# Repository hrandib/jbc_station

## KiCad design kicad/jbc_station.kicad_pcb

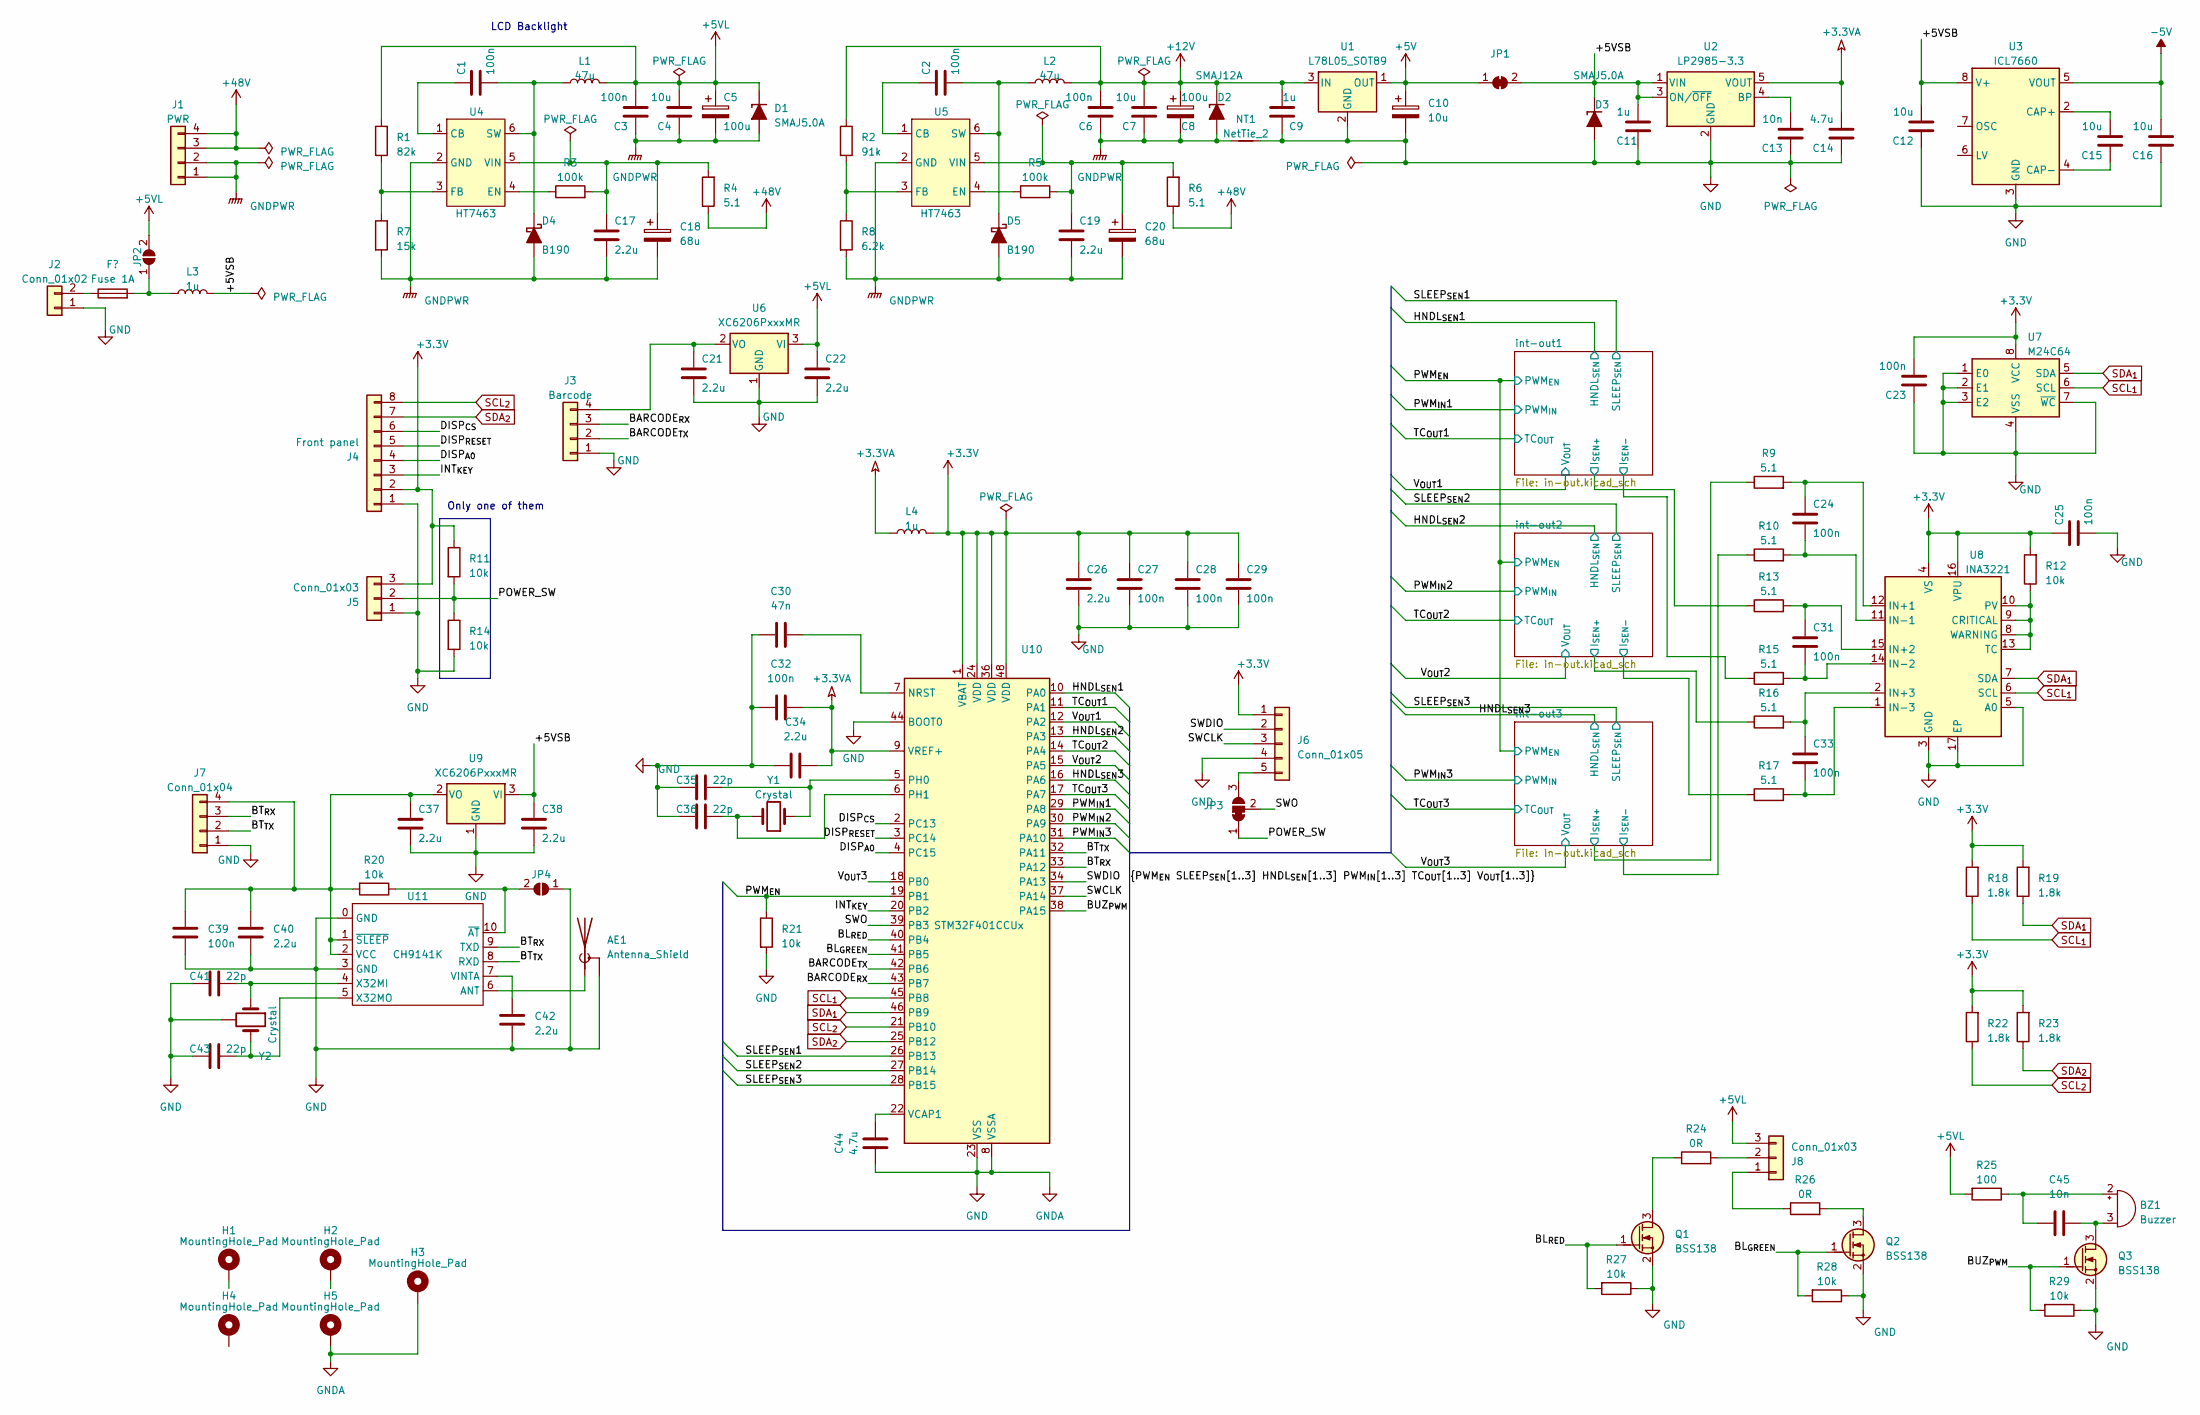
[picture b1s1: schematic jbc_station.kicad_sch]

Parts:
AE1: Antenna_Shield; Texas_SWRA117D_2.4GHz_Left
BZ1: Buzzer; BUZ_5020
C1, C2, C3, C6, C23, C24, C25, C31, C33: 100n; C_0805_2012Metric
C4, C7, C12, C15, C16: 10u; C_0805_2012Metric
C5, C8: 100u; C_Radial_D8.0mm_H11.5mm_P3.50mm
C9, C11: 1u; C_0805_2012Metric
C10: 10u; C_1812_4532Metric
C13, C45: 10n; C_0805_2012Metric
C14: 4.7u; C_0805_2012Metric
C17, C19, C21, C22, C26, C34, C37, C38: 2.2u; C_0805_2012Metric
C18, C20: 68u; C_Radial_D8.0mm_H11.5mm_P3.50mm
C27, C28, C29, C32, C39: 100n; C_0603_1608Metric_Pad1.08x0.95mm_HandSolder
C30: 47n; C_0805_2012Metric
C35, C36, C41, C43: 22p; C_0805_2012Metric
C40, C42: 2.2u; C_1206_3216Metric_Pad1.33x1.80mm_HandSolder
C44: 4.7u; C_1206_3216Metric_Pad1.33x1.80mm_HandSolder
D1, D3: SMAJ5.0A; D_SMA
D2: SMAJ12A; D_SMA
D4, D5: B190; D_SMA
F1: Fuse 1A; Fuseholder_Littelfuse_Nano2_154x
H1, H2, H3, H4, H5: MountingHole_Pad; MountingHole_3.2mm_M3_DIN965_Pad_TopBottom
J1: PWR; PhoenixContact_MCV_1,5_4-G-3.5_1x04_P3.50mm_Vertical
J2: Conn_01x02; JST_EH_B2B-EH-A_1x02_P2.50mm_Vertical
J3: Barcode; JST_EH_B4B-EH-A_1x04_P2.50mm_Vertical
J4: Front panel; JST_EH_B8B-EH-A_1x08_P2.50mm_Vertical
J5, J8: Conn_01x03; JST_EH_B3B-EH-A_1x03_P2.50mm_Vertical
J6: Conn_01x05; PinHeader_1x05_P2.54mm_Vertical
J7: Conn_01x04; PinHeader_1x04_P2.54mm_Vertical
JP1: SolderJumper_2_Bridged; SolderJumper-2_P1.3mm_Bridged_RoundedPad1.0x1.5mm
JP2, JP4: SolderJumper_2_Open; SolderJumper-2_P1.3mm_Open_TrianglePad1.0x1.5mm
JP3: SolderJumper_3_Bridged12; SolderJumper-3_P1.3mm_Bridged12_RoundedPad1.0x1.5mm_NumberL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
L1, L2: 47u; L_7.3x7.3_H3.5
L3, L4: 1u; L_1206_3216Metric_Pad1.22x1.90mm_HandSolder
NT1: NetTie_2; NetTie-2_SMD_Pad2.0mm
Q1, Q2, Q3: BSS138; SOT-23
R1: 82k; R_0603_1608Metric_Pad0.98x0.95mm_HandSolder
R2: 91k; R_0603_1608Metric_Pad0.98x0.95mm_HandSolder
R3, R5: 100k; R_0603_1608Metric_Pad0.98x0.95mm_HandSolder
R4, R6: 5.1; R_1206_3216Metric_Pad1.30x1.75mm_HandSolder
R7: 15k; R_0603_1608Metric_Pad0.98x0.95mm_HandSolder
R8: 6.2k; R_0603_1608Metric_Pad0.98x0.95mm_HandSolder
R9, R10, R13, R15, R16, R17: 5.1; R_0805_2012Metric_Pad1.20x1.40mm_HandSolder
R11, R14, R20, R21, R27, R28, R29: 10k; R_0805_2012Metric_Pad1.20x1.40mm_HandSolder
R12: 10k; R_0603_1608Metric_Pad0.98x0.95mm_HandSolder
R18, R19, R22, R23: 1.8k; R_0603_1608Metric_Pad0.98x0.95mm_HandSolder
R24, R26: 0R; R_1206_3216Metric_Pad1.30x1.75mm_HandSolder
R25: 100; R_0805_2012Metric_Pad1.20x1.40mm_HandSolder
U1: L78L05_SOT89; SOT-89-3
U2: LP2985-3.3; SOT-23-5
U3: ICL7660; SOIC-8_3.9x4.9mm_P1.27mm
U4, U5: HT7463; SOT-23-6_Handsoldering
U6, U9: XC6206PxxxMR; SOT-23-3
U7: M24C64; SOIC-8_3.9x4.9mm_P1.27mm
U8: INA3221; Texas_RGV_S-PVQFN-N16_EP2.1x2.1mm
U10: STM32F401CCUx; QFN-48-1EP_7x7mm_P0.5mm_EP5.6x5.6mm
U11: CH9141K; ESSOP-10_3.9x4.9mm_P1.00mm
Y1: Crystal; Crystal_SMD_5032-2Pin_5.0x3.2mm
Y2: Crystal; Crystal_SMD_3225-4Pin_3.2x2.5mm_HandSoldering

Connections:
+3.3V: C23.2, C25.1, C26.1, C27.1, C28.1, C29.1, J4.2, J5.3, J6.1, L4.2, R11.1, R12.2, R18.2, R19.2, R22.2, R23.2, U7.8 (VCC), U8.4 (VS), U8.16 (VPU), U10.1 (VBAT), U10.24 (VDD), U10.36 (VDD), U10.48 (VDD); also elsewhere on the board
+3.3VA: C14.2, C32.2, C34.2, L4.1, U2.5 (VOUT), U10.9 (VREF+)
+5V: C10.1, JP1.1 (A), U1.1 (OUT); also elsewhere on the board
+5VL: C3.2, C4.2, C5.1, C22.1, D1.1 (K), J8.3, JP2.2 (B), L1.2, R1.1, R25.2, U6.3 (VI)
+12V: C6.2, C7.2, C8.1, C9.2, D2.1 (K), L2.2, R2.1, U1.3 (IN); also elsewhere on the board
+48V: J1.3, J1.4, R4.1, R6.1; also elsewhere on the board
-5V: C16.2, U3.5 (VOUT); also elsewhere on the board
/+5VSB: C11.2, C12.2, C38.1, D3.1 (K), JP1.2 (B), L3.2, U2.1 (VIN), U2.3 (ON/~OFF), U3.8 (V+), U9.3 (VI)
/BARCODE_{RX}: J3.3, U10.43 (PB7)
/BARCODE_{TX}: J3.2, U10.42 (PB6)
/BL_{GREEN}: Q2.1 (G), R28.2, U10.41 (PB5)
/BL_{RED}: Q1.1 (G), R27.2, U10.40 (PB4)
/BT_{RX}: J7.3, U10.33 (PA12), U11.9 (TXD)
/BT_{TX}: J7.2, U10.32 (PA11), U11.8 (RXD)
/BUZ_{PWM}: Q3.1 (G), R29.2, U10.38 (PA15)
/DISP_{A0}: J4.4, U10.4 (PC15)
/DISP_{CS}: J4.6, U10.2 (PC13)
/DISP_{RESET}: J4.5, U10.3 (PC14)
/HNDL_{SEN}1: U10.10 (PA0); also elsewhere on the board
/HNDL_{SEN}2: U10.13 (PA3); also elsewhere on the board
/HNDL_{SEN}3: U10.16 (PA6); also elsewhere on the board
/INT_{KEY}: J4.3, U10.20 (PB2)
/POWER_SW: J5.2, JP3.1 (A), R11.2, R14.1
/PWM_{EN}: R21.1, U10.19 (PB1); also elsewhere on the board
/PWM_{IN}1: U10.29 (PA8); also elsewhere on the board
/PWM_{IN}2: U10.30 (PA9); also elsewhere on the board
/PWM_{IN}3: U10.31 (PA10); also elsewhere on the board
/SLEEP_{SEN}1: U10.26 (PB13); also elsewhere on the board
/SLEEP_{SEN}2: U10.27 (PB14); also elsewhere on the board
/SLEEP_{SEN}3: U10.28 (PB15); also elsewhere on the board
/SWCLK: J6.3, U10.37 (PA14)
/SWDIO: J6.2, U10.34 (PA13)
/SWO: JP3.2 (C), U10.39 (PB3)
/TC_{OUT}1: U10.11 (PA1); also elsewhere on the board
/TC_{OUT}2: U10.14 (PA4); also elsewhere on the board
/TC_{OUT}3: U10.17 (PA7); also elsewhere on the board
/V_{OUT}1: U10.12 (PA2); also elsewhere on the board
/V_{OUT}2: U10.15 (PA5); also elsewhere on the board
/V_{OUT}3: U10.18 (PB0); also elsewhere on the board
/int-out1/I_{SEN+}: R13.1; also elsewhere on the board
/int-out1/I_{SEN-}: R15.1; also elsewhere on the board
/int-out2/I_{SEN+}: R16.1; also elsewhere on the board
/int-out2/I_{SEN-}: R17.1; also elsewhere on the board
/int-out3/I_{SEN+}: R9.1; also elsewhere on the board
/int-out3/I_{SEN-}: R10.1; also elsewhere on the board
GND: AE1.2 (Shield), C9.1, C10.2, C11.1, C12.1, C13.1, C14.1, C16.1, C21.2, C22.2, C23.1, C25.2, C26.2, C27.2, C28.2, C29.2, C30.1, C32.1, C34.1, C35.2, C36.2, C37.2, C38.2, C39.1, C40.1, C41.2, C42.1, C43.2, C44.1, D3.2 (A), H3.1, H5.1, J2.1, J3.1, J4.1, J5.1, J6.4, J7.1, JP4.1 (A), NT1.2, Q1.2 (S), Q2.2 (S), Q3.2 (S), R14.2, R21.2, R27.1, R28.1, R29.1, U1.2 (GND), U2.2 (GND), U3.3 (GND), U6.1 (GND), U7.1 (E0), U7.2 (E1), U7.3 (E2), U7.4 (VSS), U7.7 (~WC), U8.3 (GND), U8.5 (A0), U8.17 (EP), U9.1 (GND), U10.8 (VSSA), U10.23 (VSS), U10.35 (VSS), U10.44 (BOOT0), U10.47 (VSS), U10.49 (VSS), U11.0 (GND), U11.3 (GND), Y2.2, Y2.4; also elsewhere on the board
GNDPWR: C3.1, C4.1, C5.2, C6.1, C7.1, C8.2, C17.2, C18.2, C19.2, C20.2, D1.2 (A), D2.2 (A), D4.2 (A), D5.2 (A), J1.1, J1.2, NT1.1, R7.2, R8.2, U4.2 (GND), U5.2 (GND); also elsewhere on the board
unnamed: AE1.1 (A), U11.6 (ANT)
unnamed: BZ1.2 (+), C45.1, R25.1
unnamed: BZ1.3 (-), C45.2, Q3.3 (D)
unnamed: C1.2, D4.1 (K), L1.1, U4.6 (SW)
unnamed: C2.2, D5.1 (K), L2.1, U5.6 (SW)
unnamed: F1.1, J2.2
unnamed: C21.1, J3.4, U6.2 (VO)
unnamed: J6.5, JP3.3 (B)
unnamed: C37.1, C39.2, C40.2, J7.4, R20.2, U9.2 (VO), U11.1 (~SLEEP), U11.2 (VCC)
unnamed: J8.1, R26.1
unnamed: J8.2, R24.2
unnamed: F1.2, JP2.1 (A), L3.1
unnamed: JP4.2 (B), R20.1, U11.10 (~AT)
unnamed: Q1.3 (D), R24.1
unnamed: Q2.3 (D), R26.2
unnamed: C13.2, U2.4 (BP)
unnamed: C15.2, U3.2 (CAP+)
unnamed: C15.1, U3.4 (CAP-)
unnamed: C1.1, U4.1 (CB)
unnamed: R3.1, U4.4 (EN)
unnamed: R1.2, R7.1, U4.3 (FB)
unnamed: C17.1, C18.1, R3.2, R4.2, U4.5 (VIN)
unnamed: C2.1, U5.1 (CB)
unnamed: R5.1, U5.4 (EN)
unnamed: R2.2, R8.1, U5.3 (FB)
unnamed: C19.1, C20.1, R5.2, R6.2, U5.5 (VIN)
unnamed: R12.1, U8.8 (WARNING), U8.9 (CRITICAL), U8.10 (PV), U8.13 (TC)
unnamed: C24.1, R9.2, U8.12 (IN+1)
unnamed: C31.1, R13.2, U8.15 (IN+2)
unnamed: C33.1, R16.2, U8.2 (IN+3)
unnamed: C24.2, R10.2, U8.11 (IN-1)
unnamed: C31.2, R15.2, U8.14 (IN-2)
unnamed: C33.2, R17.2, U8.1 (IN-3)
unnamed: C30.2, U10.7 (NRST)
unnamed: C35.1, U10.5 (PH0), Y1.1
unnamed: C36.1, U10.6 (PH1), Y1.2
unnamed: C44.2, U10.22 (VCAP1)
unnamed: C42.2, U11.7 (VINTA)
unnamed: C41.1, U11.4 (X32MI), Y2.1
unnamed: C43.1, U11.5 (X32MO), Y2.3
SCL_{1}: R18.1, U7.6 (SCL), U8.6 (SCL), U10.45 (PB8)
SCL_{2}: J4.8, R22.1, U10.21 (PB10)
SDA_{1}: R19.1, U7.5 (SDA), U8.7 (SDA), U10.46 (PB9)
SDA_{2}: J4.7, R23.1, U10.25 (PB12)

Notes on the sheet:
LCD Backlight
Only one of them

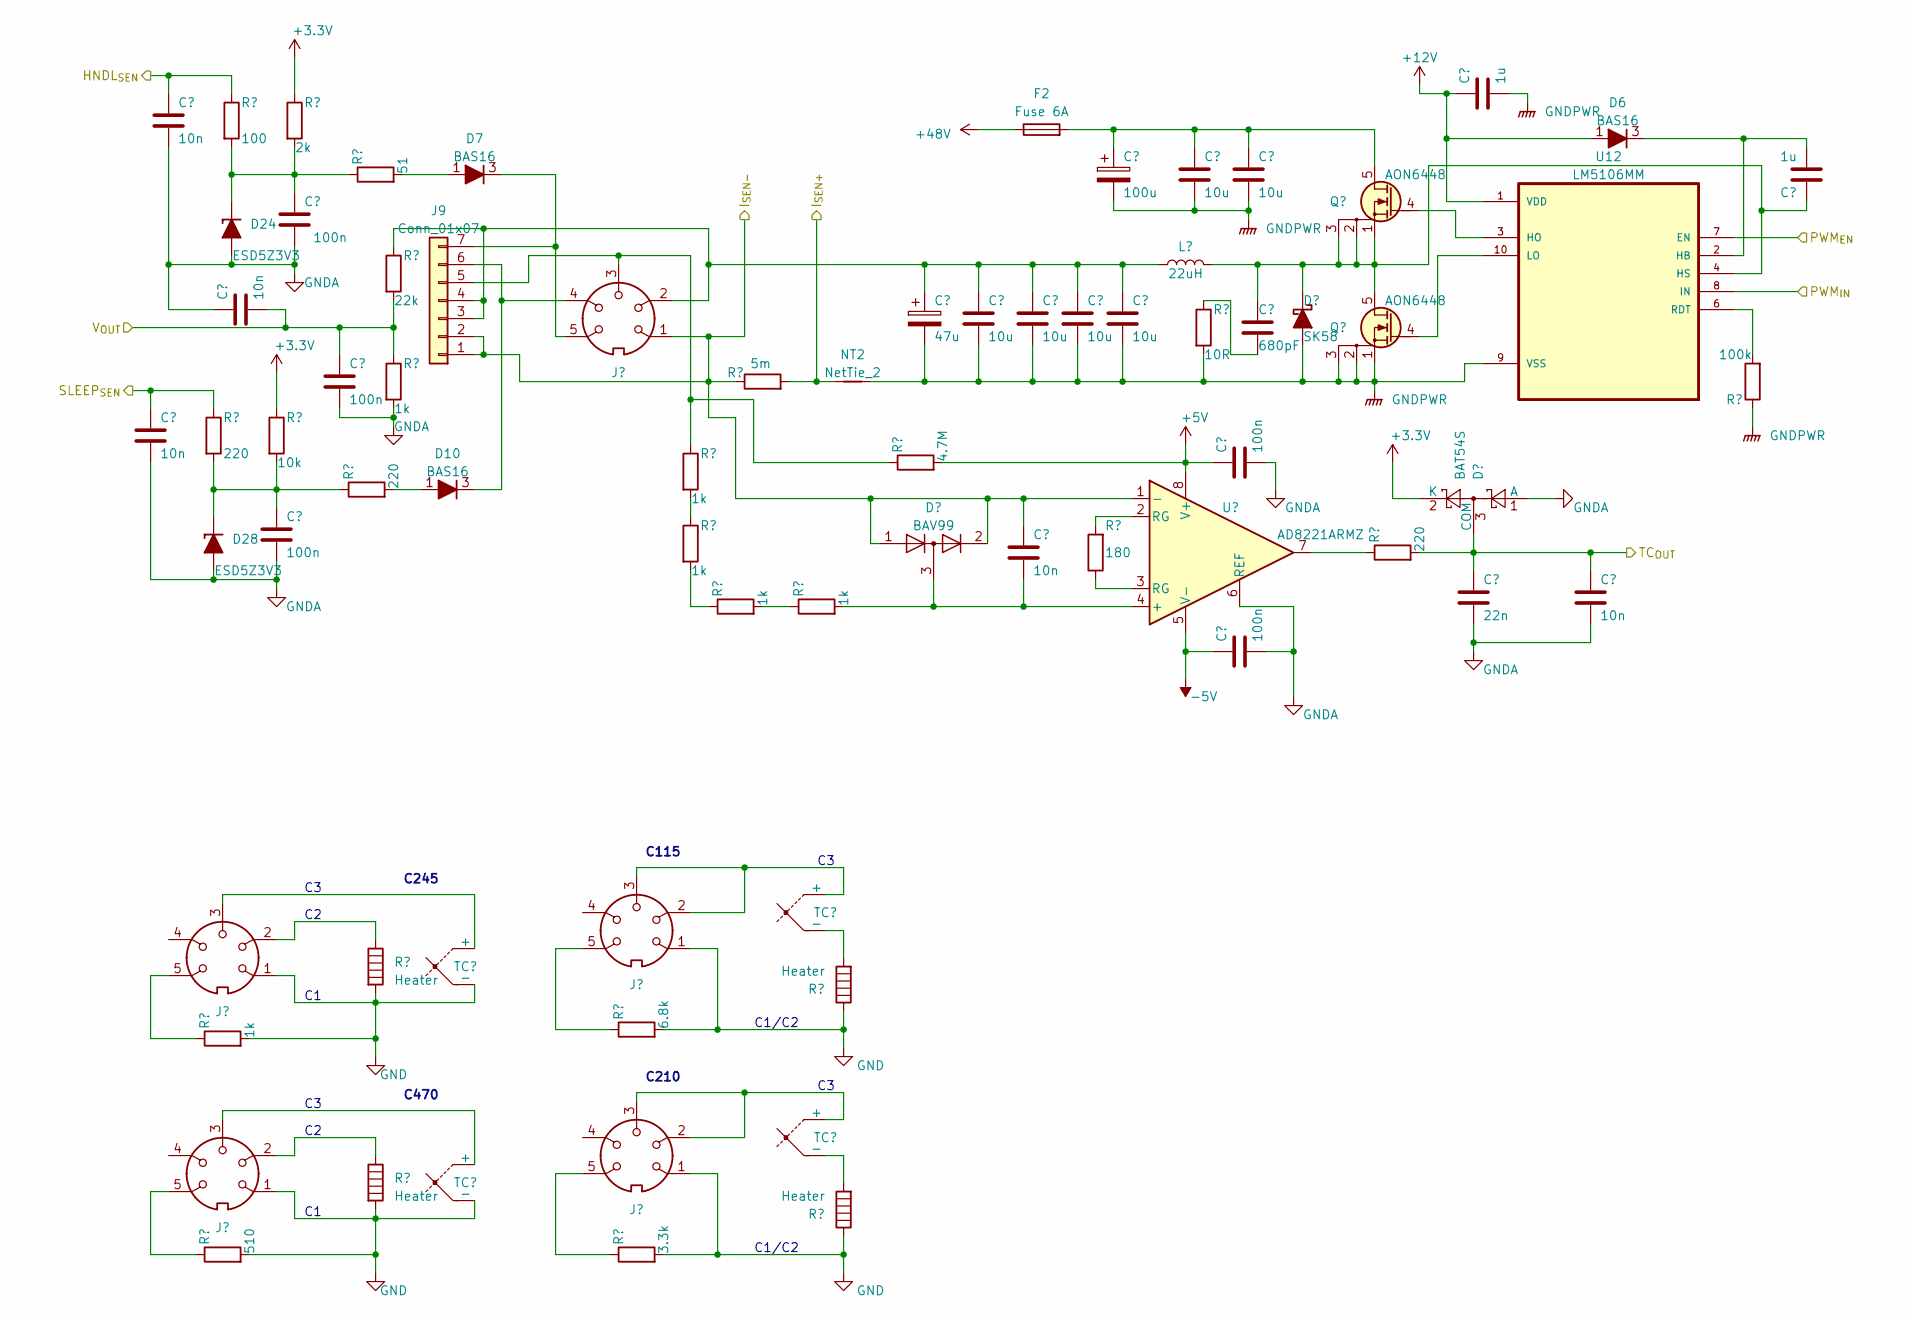
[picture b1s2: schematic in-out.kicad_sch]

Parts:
C46, C51: 1u; C_1206_3216Metric
C47, C53, C61, C66: 10n; C_0402_1005Metric
C48: 100u; C_Radial_D8.0mm_H11.5mm_P3.50mm
C49, C50, C55, C56, C57, C58: 10u; C_2220_5650Metric
C52, C60, C62, C63, C67: 100n; C_0603_1608Metric_Pad1.08x0.95mm_HandSolder
C54: 47u; C_Radial_D8.0mm_H11.5mm_P3.50mm
C59: 680pF; C_0805_2012Metric
C64: 10n; C_0805_2012Metric
C65: 22n; C_0805_2012Metric
D6, D7, D10: BAS16; SOT-23
D9: SK58; D_SMB-SMC_Universal
D11: BAT54S; SOT-23
D13: BAV99; SOT-23
D24: ESD5Z3V3; D_SOD-523_TVS
D28: ESD5Z3V3; D_SOD-523
F2: Fuse 6A; Fuseholder_Littelfuse_Nano2_154x
J9: Conn_01x07; JST_EH_B7B-EH-A_1x07_P2.50mm_Vertical
J10, J11, J12, J13, J14: DIN-5
L5: 22uH; L_Bourns_SRP1770TA_16.9x16.9mm
NT2: NetTie_2; NetTie-2_SMD_Pad2.0mm
Q4, Q5: AON6448; Infineon_PG-TDSON-8
R30: 100; R_0603_1608Metric_Pad0.98x0.95mm_HandSolder
R31: 2k; R_0603_1608Metric_Pad0.98x0.95mm_HandSolder
R32: 51; R_0603_1608Metric_Pad0.98x0.95mm_HandSolder
R33: 22k; R_0603_1608Metric_Pad0.98x0.95mm_HandSolder
R34: 10R; R_1206_3216Metric_Pad1.30x1.75mm_HandSolder
R35: 1k; R_0603_1608Metric_Pad0.98x0.95mm_HandSolder
R36: 5m; R_2512_6332Metric_Pad1.40x3.35mm_HandSolder
R37: 100k; R_0603_1608Metric_Pad0.98x0.95mm_HandSolder
R38, R42, R45: 220; R_0603_1608Metric_Pad0.98x0.95mm_HandSolder
R39: 10k; R_0603_1608Metric_Pad0.98x0.95mm_HandSolder
R40: 4.7M; R_1206_3216Metric_Pad1.30x1.75mm_HandSolder
R41, R43, R46, R47: 1k; R_1206_3216Metric_Pad1.30x1.75mm_HandSolder
R44: 180; R_0603_1608Metric_Pad0.98x0.95mm_HandSolder
R48, R49, R52, R53: Heater
R50: 6.8k
R51: 1k
R54: 510
R55: 3.3k; R_0603_1608Metric_Pad0.98x0.95mm_HandSolder
TC1, TC2, TC3, TC4: Thermocouple
U12: LM5106MM; MSOP-10_3x3mm_P0.5mm
U13: AD8221ARMZ; MSOP-8_3x3mm_P0.65mm

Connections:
+3.3V: D11.2 (K), R31.1, R39.1; also elsewhere on the board
+5V: C62.1, R40.2, U13.8 (V+); also elsewhere on the board
+12V: C46.1, D6.1 (A), U12.1 (VDD); also elsewhere on the board
+48V: F2.1; also elsewhere on the board
-5V: C67.1, U13.5 (V-); also elsewhere on the board
/HNDL_{SEN}1: C47.1, R30.1; also elsewhere on the board
/PWM_{EN}: U12.7 (EN); also elsewhere on the board
/PWM_{IN}1: U12.8 (IN); also elsewhere on the board
/SLEEP_{SEN}1: C61.1, R38.1; also elsewhere on the board
/TC_{OUT}1: C65.1, C66.1, D11.3 (COM), R45.2; also elsewhere on the board
/V_{OUT}1: C53.2, C60.1, R33.2, R35.1; also elsewhere on the board
/int-out1/I_{SEN+}: NT2.1, R36.2; also elsewhere on the board
/int-out1/I_{SEN-}: C64.1, D13.1 (K), D13.2 (A), J9.1, J9.2, R36.1, U13.1 (-); also elsewhere on the board
GND: C47.2, C52.2, C53.1, C60.2, C61.2, C62.2, C63.2, C65.2, C66.2, C67.2, D11.1 (A), D24.2 (A), D28.2 (A), R35.2, U13.6 (REF); also elsewhere on the board
GNDPWR: C46.2, C48.2, C49.2, C50.2, C54.2, C55.2, C56.2, C57.2, C58.2, D9.2 (A), NT2.2, Q5.1 (S), Q5.2 (S), Q5.3 (S), R34.2, R37.1, U12.9 (VSS); also elsewhere on the board
unnamed: C59.2, R34.1
unnamed: C51.2, D6.3 (K), U12.2 (HB)
unnamed: D7.1 (A), R32.2
unnamed: D7.3 (K), J9.7
unnamed: C51.1, C59.1, D9.1 (K), L5.2, Q4.1 (S), Q4.2 (S), Q4.3 (S), Q5.5 (D), U12.4 (HS)
unnamed: D10.1 (A), R42.2
unnamed: D10.3 (K), J9.6
unnamed: C54.1, C55.1, C56.1, C57.1, C58.1, J9.3, J9.4, L5.1, R33.1
unnamed: J9.5, R40.1, R41.1
unnamed: J11.1, J12.1, J13.1, J14.1, R48.2, R49.1, R50.2, R51.2, R52.2, R53.1, R54.2, R55.2, TC2.2 (-), TC4.2 (-)
unnamed: J11.2, J11.3, TC1.1 (+)
unnamed: J11.5, R50.1
unnamed: J12.2, R48.1
unnamed: J12.3, TC2.1 (+)
unnamed: J12.5, R51.1
unnamed: J13.2, J13.3, TC3.1 (+)
unnamed: J13.5, R55.1
unnamed: J14.2, R52.1
unnamed: J14.3, TC4.1 (+)
unnamed: J14.5, R54.1
unnamed: C48.1, C49.1, C50.1, F2.2, Q4.5 (D)
unnamed: Q4.4 (G), U12.3 (HO)
unnamed: Q5.4 (G), U12.10 (LO)
unnamed: R41.2, R43.1
unnamed: R43.2, R46.1
unnamed: R44.1, U13.3 (RG)
unnamed: R44.2, U13.2 (RG)
unnamed: R45.1, U13.7
unnamed: R46.2, R47.1
unnamed: R49.2, TC1.2 (-)
unnamed: R53.2, TC3.2 (-)
unnamed: R37.2, U12.6 (RDT)
unnamed: C64.2, D13.3 (K), R47.2, U13.4 (+)

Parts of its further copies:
C68, C73, C90, C95: 1u; C_1206_3216Metric
C69, C75, C83, C88, C91, C97, C105, C110: 10n; C_0402_1005Metric
C70, C92: 100u; C_Radial_D8.0mm_H11.5mm_P3.50mm
C71, C72, C77, C78, C79, C80, C93, C94, C99, C100, C101, C102: 10u; C_2220_5650Metric
C74, C82, C84, C85, C89, C96, C104, C106, C107, C111: 100n; C_0603_1608Metric_Pad1.08x0.95mm_HandSolder
C76, C98: 47u; C_Radial_D8.0mm_H11.5mm_P3.50mm
C81, C103: 680pF; C_0805_2012Metric
C86, C108: 10n; C_0805_2012Metric
C87, C109: 22n; C_0805_2012Metric
D8, D16: ESD5Z3V3; D_SOD-523_TVS
D12, D20: ESD5Z3V3; D_SOD-523
D14, D15, D18, D22, D23, D26: BAS16; SOT-23
D17, D25: SK58; D_SMB-SMC_Universal
D19, D27: BAT54S; SOT-23
D21, D29: BAV99; SOT-23
F3, F4: Fuse 6A; Fuseholder_Littelfuse_Nano2_154x
J15, J21: Conn_01x07; JST_EH_B7B-EH-A_1x07_P2.50mm_Vertical
L6, L7: 22uH; L_Bourns_SRP1770TA_16.9x16.9mm
NT3, NT4: NetTie_2; NetTie-2_SMD_Pad2.0mm
Q6, Q7, Q8, Q9: AON6448; Infineon_PG-TDSON-8
R56, R82: 100; R_0603_1608Metric_Pad0.98x0.95mm_HandSolder
R57, R83: 2k; R_0603_1608Metric_Pad0.98x0.95mm_HandSolder
R58, R84: 51; R_0603_1608Metric_Pad0.98x0.95mm_HandSolder
R59, R85: 22k; R_0603_1608Metric_Pad0.98x0.95mm_HandSolder
R60, R86: 10R; R_1206_3216Metric_Pad1.30x1.75mm_HandSolder
R61, R87: 1k; R_0603_1608Metric_Pad0.98x0.95mm_HandSolder
R62, R88: 5m; R_2512_6332Metric_Pad1.40x3.35mm_HandSolder
R63, R89: 100k; R_0603_1608Metric_Pad0.98x0.95mm_HandSolder
R64, R68, R71, R90, R94, R97: 220; R_0603_1608Metric_Pad0.98x0.95mm_HandSolder
R65, R91: 10k; R_0603_1608Metric_Pad0.98x0.95mm_HandSolder
R66, R92: 4.7M; R_1206_3216Metric_Pad1.30x1.75mm_HandSolder
R67, R69, R72, R73, R93, R95, R98, R99: 1k; R_1206_3216Metric_Pad1.30x1.75mm_HandSolder
R70, R96: 180; R_0603_1608Metric_Pad0.98x0.95mm_HandSolder
U14, U16: LM5106MM; MSOP-10_3x3mm_P0.5mm
U15, U17: AD8221ARMZ; MSOP-8_3x3mm_P0.65mm

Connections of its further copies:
+3.3V: D19.2 (K), D27.2 (K), R57.1, R65.1, R83.1, R91.1; also elsewhere on the board
+5V: C84.1, C106.1, R66.2, R92.2, U15.8 (V+), U17.8 (V+); also elsewhere on the board
+12V: C68.1, C90.1, D14.1 (A), D22.1 (A), U14.1 (VDD), U16.1 (VDD); also elsewhere on the board
+48V: F3.1, F4.1; also elsewhere on the board
-5V: C89.1, C111.1, U15.5 (V-), U17.5 (V-); also elsewhere on the board
/HNDL_{SEN}2: C69.1, R56.1; also elsewhere on the board
/HNDL_{SEN}3: C91.1, R82.1; also elsewhere on the board
/PWM_{EN}: U14.7 (EN), U16.7 (EN); also elsewhere on the board
/PWM_{IN}2: U14.8 (IN); also elsewhere on the board
/PWM_{IN}3: U16.8 (IN); also elsewhere on the board
/SLEEP_{SEN}2: C83.1, R64.1; also elsewhere on the board
/SLEEP_{SEN}3: C105.1, R90.1; also elsewhere on the board
/TC_{OUT}2: C87.1, C88.1, D19.3 (COM), R71.2; also elsewhere on the board
/TC_{OUT}3: C109.1, C110.1, D27.3 (COM), R97.2; also elsewhere on the board
/V_{OUT}2: C75.2, C82.1, R59.2, R61.1; also elsewhere on the board
/V_{OUT}3: C97.2, C104.1, R85.2, R87.1; also elsewhere on the board
/int-out2/I_{SEN+}: NT3.1, R62.2; also elsewhere on the board
/int-out2/I_{SEN-}: C86.1, D21.1 (K), D21.2 (A), J15.1, J15.2, R62.1, U15.1 (-); also elsewhere on the board
/int-out3/I_{SEN+}: NT4.1, R88.2; also elsewhere on the board
/int-out3/I_{SEN-}: C108.1, D29.1 (K), D29.2 (A), J21.1, J21.2, R88.1, U17.1 (-); also elsewhere on the board
GND: C69.2, C74.2, C75.1, C82.2, C83.2, C84.2, C85.2, C87.2, C88.2, C89.2, C91.2, C96.2, C97.1, C104.2, C105.2, C106.2, C107.2, C109.2, C110.2, C111.2, D8.2 (A), D12.2 (A), D16.2 (A), D19.1 (A), D20.2 (A), D27.1 (A), R61.2, R87.2, U15.6 (REF), U17.6 (REF); also elsewhere on the board
GNDPWR: C68.2, C70.2, C71.2, C72.2, C76.2, C77.2, C78.2, C79.2, C80.2, C90.2, C92.2, C93.2, C94.2, C98.2, C99.2, C100.2, C101.2, C102.2, D17.2 (A), D25.2 (A), NT3.2, NT4.2, Q7.1 (S), Q7.2 (S), Q7.3 (S), Q9.1 (S), Q9.2 (S), Q9.3 (S), R60.2, R63.1, R86.2, R89.1, U14.9 (VSS), U16.9 (VSS); also elsewhere on the board
unnamed: C81.2, R60.1
unnamed: C103.2, R86.1
unnamed: C73.2, D14.3 (K), U14.2 (HB)
unnamed: D15.1 (A), R58.2
unnamed: D15.3 (K), J15.7
unnamed: C74.1, D16.1 (K), R56.2, R57.2, R58.1
unnamed: C73.1, C81.1, D17.1 (K), L6.2, Q6.1 (S), Q6.2 (S), Q6.3 (S), Q7.5 (D), U14.4 (HS)
unnamed: D18.1 (A), R68.2
unnamed: D18.3 (K), J15.6
unnamed: C85.1, D20.1 (K), R64.2, R65.2, R68.1
unnamed: C95.2, D22.3 (K), U16.2 (HB)
unnamed: D23.1 (A), R84.2
unnamed: D23.3 (K), J21.7
unnamed: C95.1, C103.1, D25.1 (K), L7.2, Q8.1 (S), Q8.2 (S), Q8.3 (S), Q9.5 (D), U16.4 (HS)
unnamed: D26.1 (A), R94.2
unnamed: D26.3 (K), J21.6
unnamed: C76.1, C77.1, C78.1, C79.1, C80.1, J15.3, J15.4, L6.1, R59.1
unnamed: J15.5, R66.1, R67.1
unnamed: C98.1, C99.1, C100.1, C101.1, C102.1, J21.3, J21.4, L7.1, R85.1
unnamed: J21.5, R92.1, R93.1
unnamed: C70.1, C71.1, C72.1, F3.2, Q6.5 (D)
unnamed: Q6.4 (G), U14.3 (HO)
unnamed: Q7.4 (G), U14.10 (LO)
unnamed: C92.1, C93.1, C94.1, F4.2, Q8.5 (D)
unnamed: Q8.4 (G), U16.3 (HO)
unnamed: Q9.4 (G), U16.10 (LO)
unnamed: R67.2, R69.1
unnamed: R69.2, R72.1
unnamed: R70.1, U15.3 (RG)
unnamed: R70.2, U15.2 (RG)
unnamed: R71.1, U15.7
unnamed: R72.2, R73.1
unnamed: R93.2, R95.1
unnamed: R95.2, R98.1
unnamed: R96.1, U17.3 (RG)
unnamed: R96.2, U17.2 (RG)
unnamed: R97.1, U17.7
unnamed: R98.2, R99.1
unnamed: R63.2, U14.6 (RDT)
unnamed: C86.2, D21.3 (K), R73.2, U15.4 (+)
unnamed: R89.2, U16.6 (RDT)
unnamed: C108.2, D29.3 (K), R99.2, U17.4 (+)

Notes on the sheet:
C245
C1/C2
C210
C470
C115

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
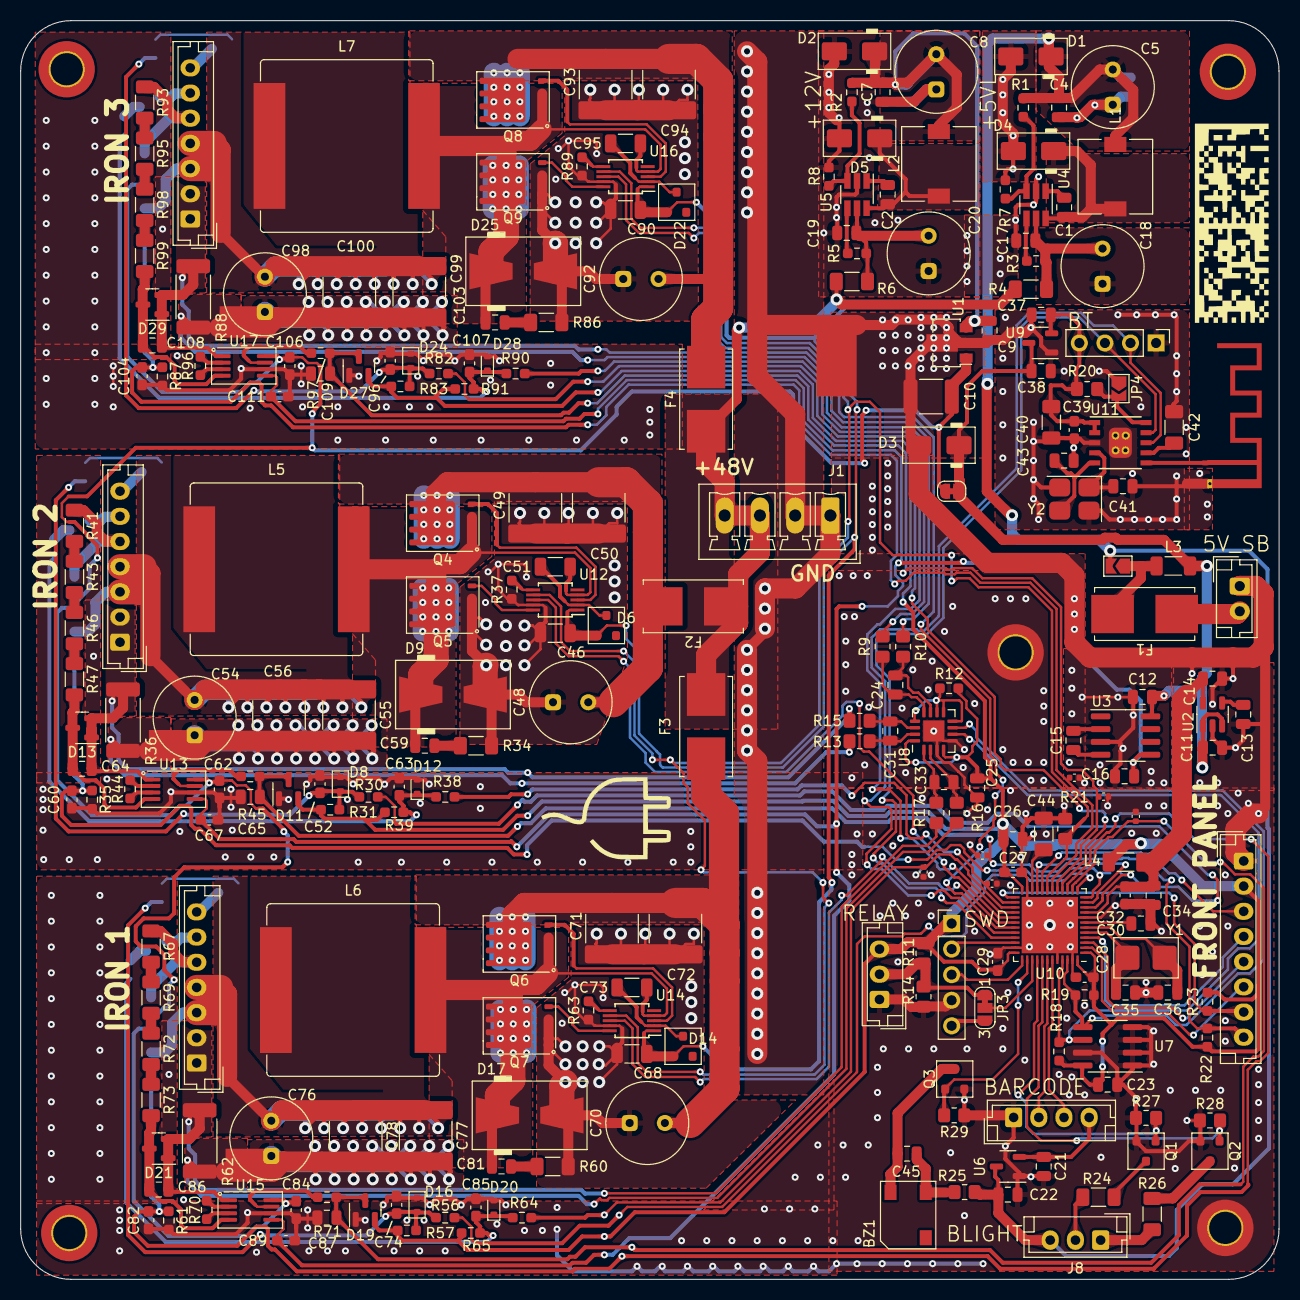
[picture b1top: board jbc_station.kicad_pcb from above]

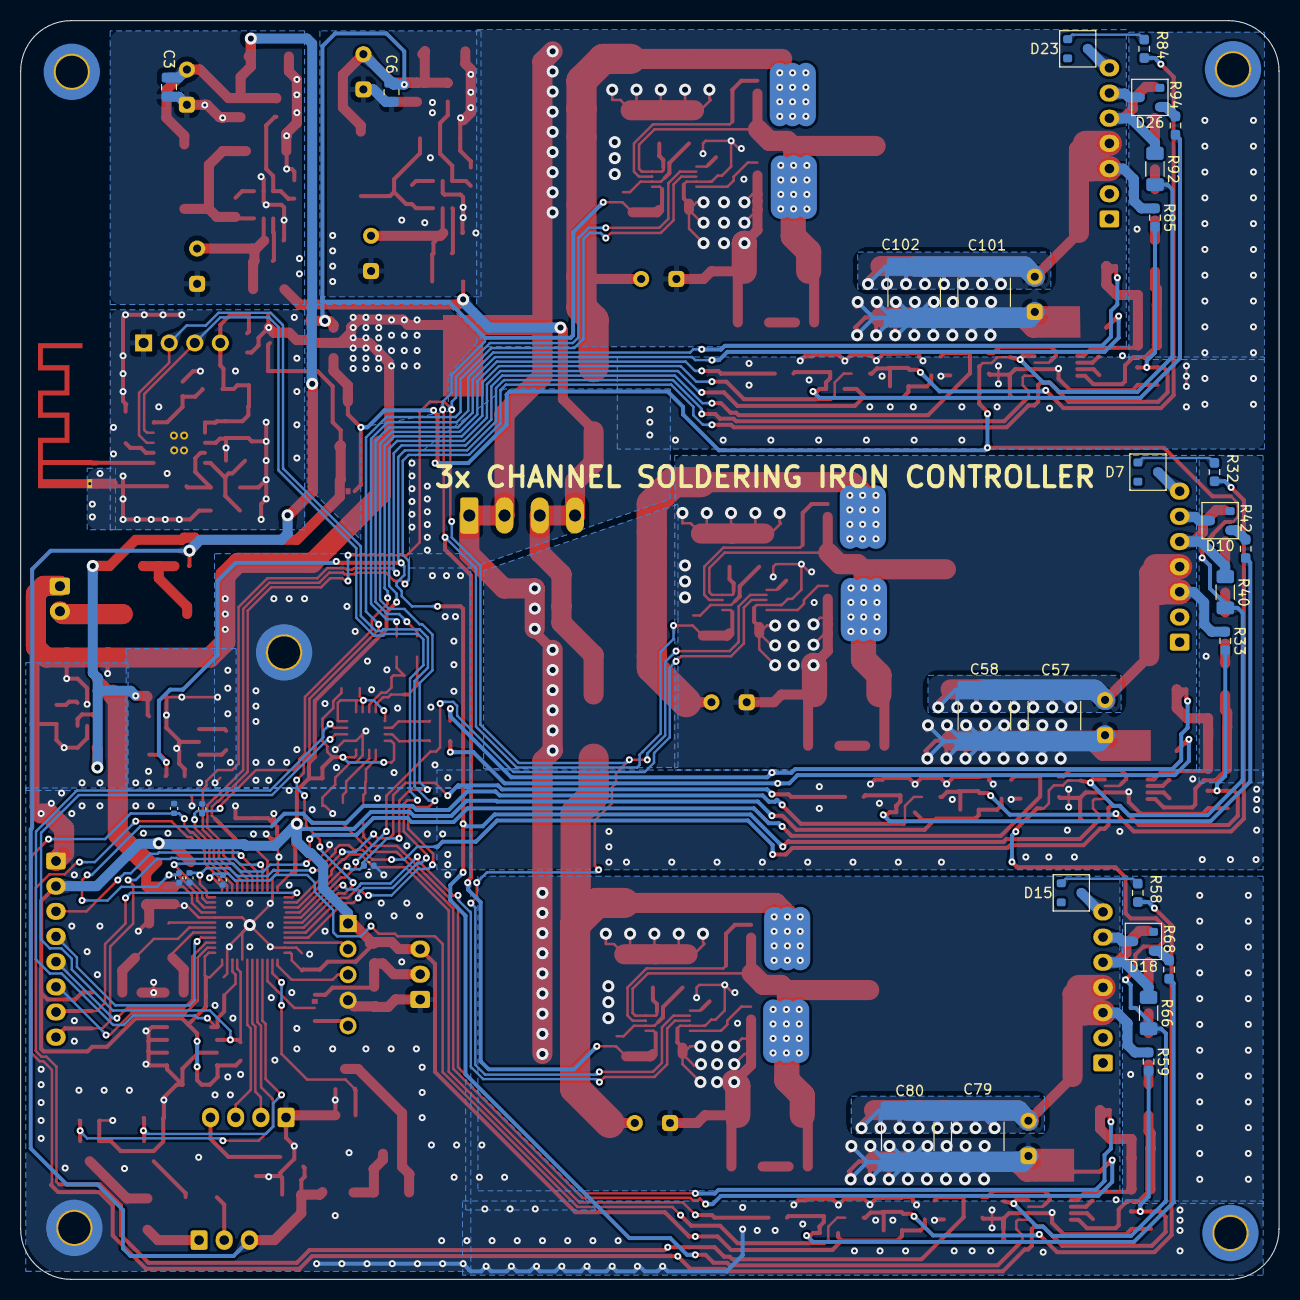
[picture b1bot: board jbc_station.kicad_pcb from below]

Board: 2 copper layers, 125.0 x 125.0 mm, 288 parts (32 on the bottom side), 157 nets.

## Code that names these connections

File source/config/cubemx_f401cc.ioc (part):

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Mcu.Name=STM32F401C(B-C)Ux
Mcu.Package=UFQFPN48
Mcu.UserName=STM32F401CCUx
PA0-WKUP.GPIOParameters=GPIO_Label,GPIO_Mode
PA0-WKUP.GPIO_Label=HNDL_SEN1
PA0-WKUP.GPIO_Mode=GPIO_MODE_ANALOG
PA0-WKUP.Signal=ADCx_IN0
PA1.GPIOParameters=GPIO_Label,GPIO_Mode
PA1.GPIO_Label=TC1
PA1.GPIO_Mode=GPIO_MODE_ANALOG
PA1.Signal=ADCx_IN1
PA10.GPIOParameters=GPIO_Speed,GPIO_Label
PA10.GPIO_Label=PWM3
PA10.GPIO_Speed=GPIO_SPEED_FREQ_MEDIUM
PA10.Signal=S_TIM1_CH3
PA11.GPIOParameters=GPIO_Speed,GPIO_Label
PA11.GPIO_Label=BT_TX
PA11.GPIO_Speed=GPIO_SPEED_FREQ_MEDIUM
PA11.Mode=Asynchronous
PA11.Signal=USART6_TX
PA12.GPIOParameters=GPIO_Speed,GPIO_Label
PA12.GPIO_Label=BT_RX
PA12.GPIO_Speed=GPIO_SPEED_FREQ_MEDIUM
PA12.Mode=Asynchronous
PA12.Signal=USART6_RX
PA13.Mode=Trace_Asynchronous_SW
PA13.Signal=SYS_JTMS-SWDIO
PA14.Mode=Trace_Asynchronous_SW
PA14.Signal=SYS_JTCK-SWCLK
PA15.GPIOParameters=GPIO_Label
PA15.GPIO_Label=BUZ
PA15.Signal=S_TIM2_CH1_ETR
PA2.GPIOParameters=GPIO_Label
PA2.GPIO_Label=VIN1
PA2.Signal=ADCx_IN2
PA3.GPIOParameters=GPIO_Label,GPIO_Mode
PA3.GPIO_Label=HNDL_SEN2
PA3.GPIO_Mode=GPIO_MODE_ANALOG
PA3.Signal=ADCx_IN3
PA4.GPIOParameters=GPIO_Label,GPIO_Mode
PA4.GPIO_Label=TC2
PA4.GPIO_Mode=GPIO_MODE_ANALOG
PA4.Signal=ADCx_IN4
PA5.GPIOParameters=GPIO_Label
PA5.GPIO_Label=VIN2
PA5.Signal=ADCx_IN5
PA6.GPIOParameters=GPIO_Label,GPIO_Mode
PA6.GPIO_Label=HNDL_SEN3
PA6.GPIO_Mode=GPIO_MODE_ANALOG
PA6.Signal=ADCx_IN6
PA7.GPIOParameters=GPIO_Label,GPIO_Mode
PA7.GPIO_Label=TC3
PA7.GPIO_Mode=GPIO_MODE_ANALOG
PA7.Signal=ADCx_IN7
PA8.GPIOParameters=GPIO_Speed,GPIO_Label
PA8.GPIO_Label=PWM1
PA8.GPIO_Speed=GPIO_SPEED_FREQ_MEDIUM
PA8.Signal=S_TIM1_CH1
PA9.GPIOParameters=GPIO_Speed,GPIO_Label
PA9.GPIO_Label=PWM2
PA9.GPIO_Speed=GPIO_SPEED_FREQ_MEDIUM
PA9.Signal=S_TIM1_CH2
PB0.GPIOParameters=GPIO_Label
PB0.GPIO_Label=VIN3
PB0.Signal=ADCx_IN8
PB1.GPIOParameters=GPIO_Speed,GPIO_Label
PB1.GPIO_Label=PWM_EN
PB1.GPIO_Speed=GPIO_SPEED_FREQ_HIGH
PB1.Signal=GPIO_Output
PB10.GPIOParameters=GPIO_PuPd,GPIO_Label
PB10.GPIO_Label=FP_RESERVED
PB10.GPIO_PuPd=GPIO_PULLUP
PB10.Signal=GPIO_Input
PB12.GPIOParameters=GPIO_Speed,GPIO_Label
PB12.GPIO_Label=SER_CLK
PB12.GPIO_Speed=GPIO_SPEED_FREQ_LOW
PB12.Signal=GPIO_Output
PB13.GPIOParameters=GPIO_PuPd,GPIO_Label,GPIO_Mode
PB13.GPIO_Label=SLEEP_SEN1
PB13.GPIO_Mode=GPIO_MODE_INPUT
PB13.GPIO_PuPd=GPIO_PULLUP
PB13.Signal=GPIO_Input
PB14.GPIOParameters=GPIO_PuPd,GPIO_Label,GPIO_Mode
PB14.GPIO_Label=SLEEP_SEN2
PB14.GPIO_Mode=GPIO_MODE_INPUT
PB14.GPIO_PuPd=GPIO_PULLUP
PB14.Signal=GPIO_Input
PB15.GPIOParameters=GPIO_PuPd,GPIO_Label,GPIO_Mode
PB15.GPIO_Label=SLEEP_SEN3
PB15.GPIO_Mode=GPIO_MODE_INPUT
PB15.GPIO_PuPd=GPIO_PULLUP
PB15.Signal=GPIO_Input
PB2.GPIOParameters=GPIO_PuPd,GPIO_Label
PB2.GPIO_Label=KEY_POLL
PB2.GPIO_PuPd=GPIO_PULLDOWN
PB2.Signal=GPIO_Input
PB3.Mode=Trace_Asynchronous_SW
PB3.Signal=SYS_JTDO-SWO
PB4.GPIOParameters=GPIO_PuPd,GPIO_Label
PB4.GPIO_Label=BL_RED
PB4.GPIO_PuPd=GPIO_PULLDOWN
PB4.Signal=S_TIM3_CH1
PB5.GPIOParameters=GPIO_PuPd,GPIO_Label
PB5.GPIO_Label=BL_GREEN
PB5.GPIO_PuPd=GPIO_PULLDOWN
PB5.Signal=S_TIM3_CH2
PB6.GPIOParameters=GPIO_Speed,GPIO_Label
PB6.GPIO_Label=BARCODE_TX
PB6.GPIO_Speed=GPIO_SPEED_FREQ_MEDIUM
PB6.Mode=Asynchronous
PB6.Signal=USART1_TX
PB7.GPIOParameters=GPIO_Speed,GPIO_Label
PB7.GPIO_Label=BARCODE_RX
PB7.GPIO_Speed=GPIO_SPEED_FREQ_MEDIUM
PB7.Mode=Asynchronous
PB7.Signal=USART1_RX
PB8.GPIOParameters=GPIO_Speed
PB8.GPIO_Speed=GPIO_SPEED_FREQ_LOW
PB8.Mode=I2C
PB8.Signal=I2C1_SCL
PB9.GPIOParameters=GPIO_Speed
PB9.GPIO_Speed=GPIO_SPEED_FREQ_LOW
PB9.Mode=I2C
PB9.Signal=I2C1_SDA
PC13-ANTI_TAMP.GPIOParameters=GPIO_Speed,PinState,GPIO_Label,GPIO_ModeDefaultOutputPP
PC13-ANTI_TAMP.GPIO_Label=DISP_CS
PC13-ANTI_TAMP.GPIO_ModeDefaultOutputPP=GPIO_MODE_OUTPUT_PP
PC13-ANTI_TAMP.GPIO_Speed=GPIO_SPEED_FREQ_LOW
PC13-ANTI_TAMP.PinState=GPIO_PIN_RESET
PC13-ANTI_TAMP.Signal=GPIO_Output
PC14-OSC32_IN.GPIOParameters=GPIO_Speed,PinState,GPIO_Label,GPIO_ModeDefaultOutputPP
PC14-OSC32_IN.GPIO_Label=DISP_A0_DAT
PC14-OSC32_IN.GPIO_ModeDefaultOutputPP=GPIO_MODE_OUTPUT_PP
PC14-OSC32_IN.GPIO_Speed=GPIO_SPEED_FREQ_LOW
PC14-OSC32_IN.PinState=GPIO_PIN_RESET
PC14-OSC32_IN.Signal=GPIO_Output
PC15-OSC32_OUT.GPIOParameters=GPIO_Speed,PinState,GPIO_Label,GPIO_ModeDefaultOutputPP
PC15-OSC32_OUT.GPIO_Label=DISP_RESET
PC15-OSC32_OUT.GPIO_ModeDefaultOutputPP=GPIO_MODE_OUTPUT_PP
PC15-OSC32_OUT.GPIO_Speed=GPIO_SPEED_FREQ_LOW
PC15-OSC32_OUT.PinState=GPIO_PIN_RESET
PC15-OSC32_OUT.Signal=GPIO_Output
PH0\ -\ OSC_IN.Mode=HSE-External-Oscillator
PH0\ -\ OSC_IN.Signal=RCC_OSC_IN
PH1\ -\ OSC_OUT.Mode=HSE-External-Oscillator
PH1\ -\ OSC_OUT.Signal=RCC_OSC_OUT
RCC.HSE_VALUE=8000000
RCC.SYSCLKFreq_VALUE=84000000
RCC.SYSCLKSource=RCC_SYSCLKSOURCE_PLLCLK
board=custom

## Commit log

2023-01-08 Initial
2023-01-08 Add ChibiOS submodules
2023-02-12 Update modules wiring
2023-02-12 General cleanup
2023-02-12 Update board/hal config
2023-02-12 Sensor handler impl begin
2023-03-24 Cleanup the template
2023-03-24 Add compiler FPU flags
2023-03-26 Update .clang-format to preserve ChibiOS headers position
2023-03-26 Design input/output power stage
2023-03-26 Add regulators
2023-03-26 Add current sensor
2023-03-26 Most of the main board is done
2023-04-12 Main board: add BT
2023-04-17 PCB routing initial
2023-04-20 Route power stage
2023-04-20 Route DC-DCs, BT
2023-04-21 Route LDOs
2023-04-21 Route finish
2023-04-22 Add more filtering caps for ADC
2023-04-22 Silkscreen cleanup
2023-04-22 Various small fixes
2023-04-23 Add logo and text
2023-04-23 Fix silkscreen
2023-04-23 Change coordinates origin
2023-04-28 Minor fixes in silkscreen and routing
2023-04-28 Create LICENSE
2023-04-28 Update mcuconf and halconf for nucleo
2023-04-28 Update board.h for nucleo
2023-04-28 Blinker in the working state
2023-04-29 Port C++ gpio driver
2023-04-30 Gpio driver in the working state
2023-04-30 Add display driver skeleton
2023-04-30 Add display init sequence check
2023-04-30 Add LVGL as submodule
2023-04-30 Add 180 deg rotation option
2023-04-30 Add lvgl to the Qbs build. Initial
2023-05-01 LVGL in the compilable state
2023-05-01 Switch to the release lvgl branch. lv_conf tweaks
2023-05-02 Attempt to integrate the display to LVGL. Still broken
2023-05-02 Tweak .clangd file for C files
2023-05-03 Add u8g2 lib as submodule
2023-05-03 LVGL is in a working state
2023-05-03 Add test screen
2023-05-03 Add Chibios related utils
2023-05-03 Add serial logging
2023-05-03 Fix Y dimension pixel filling
2023-05-08 Add main screen skeleton
2023-05-10 Change MCU type
2023-05-10 Various minor fixes based on production samples
2023-05-12 Add front panel schematic based on 74HC164
2023-05-14 Add basic support of monospace fonts in the glcd format
2023-05-15 Support of all monospace fonts from SSD1306Ascii repo
2023-05-20 Fix front panel sch
2023-05-20 General cleanup. Remove u8g2 submodule
    Add ShiftReg helper class
    Add Hooge font
2023-05-20 Add batch pin init helper function
2023-05-20 Make s1d157xx driver compatible with the shift register serialization
2023-05-20 Fix ShiftReg wrapper implementation
2023-05-20 Add the display-via-shiftreg checking sequence
2023-05-21 Implement keyboard polling
2023-05-21 Improve reliability of the display driver with shift register
2023-05-27 Remove display init delay
2023-05-27 Sch: fix front panel labels naming
2023-05-27 Change HW config to the target STM32F401xC
2023-05-27 Update display pinout and timings for the target HW
2023-05-28 Implement basic backlight driver
2023-05-28 Add buzzer driver
2023-07-01 Refactor and cleanup GFX font renderer
2023-07-01 Cleanup display_handler
    Move UI template to the separate unit
2023-07-03 Remove version check in the Hooge font
2023-07-03 Remove Hooge font from display_handler dependency
2023-07-03 Minor fixes in main_screen template
2023-07-03 Static styles: add fonts
2023-09-14 Remove unused files
2023-09-14 Add const font styles
2023-09-14 Add section styles
2023-09-17 Add initial InputHandler implementation
